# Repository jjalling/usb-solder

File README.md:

# usb-solder

USB-PD soldering iron, using Weller RT soldering tips

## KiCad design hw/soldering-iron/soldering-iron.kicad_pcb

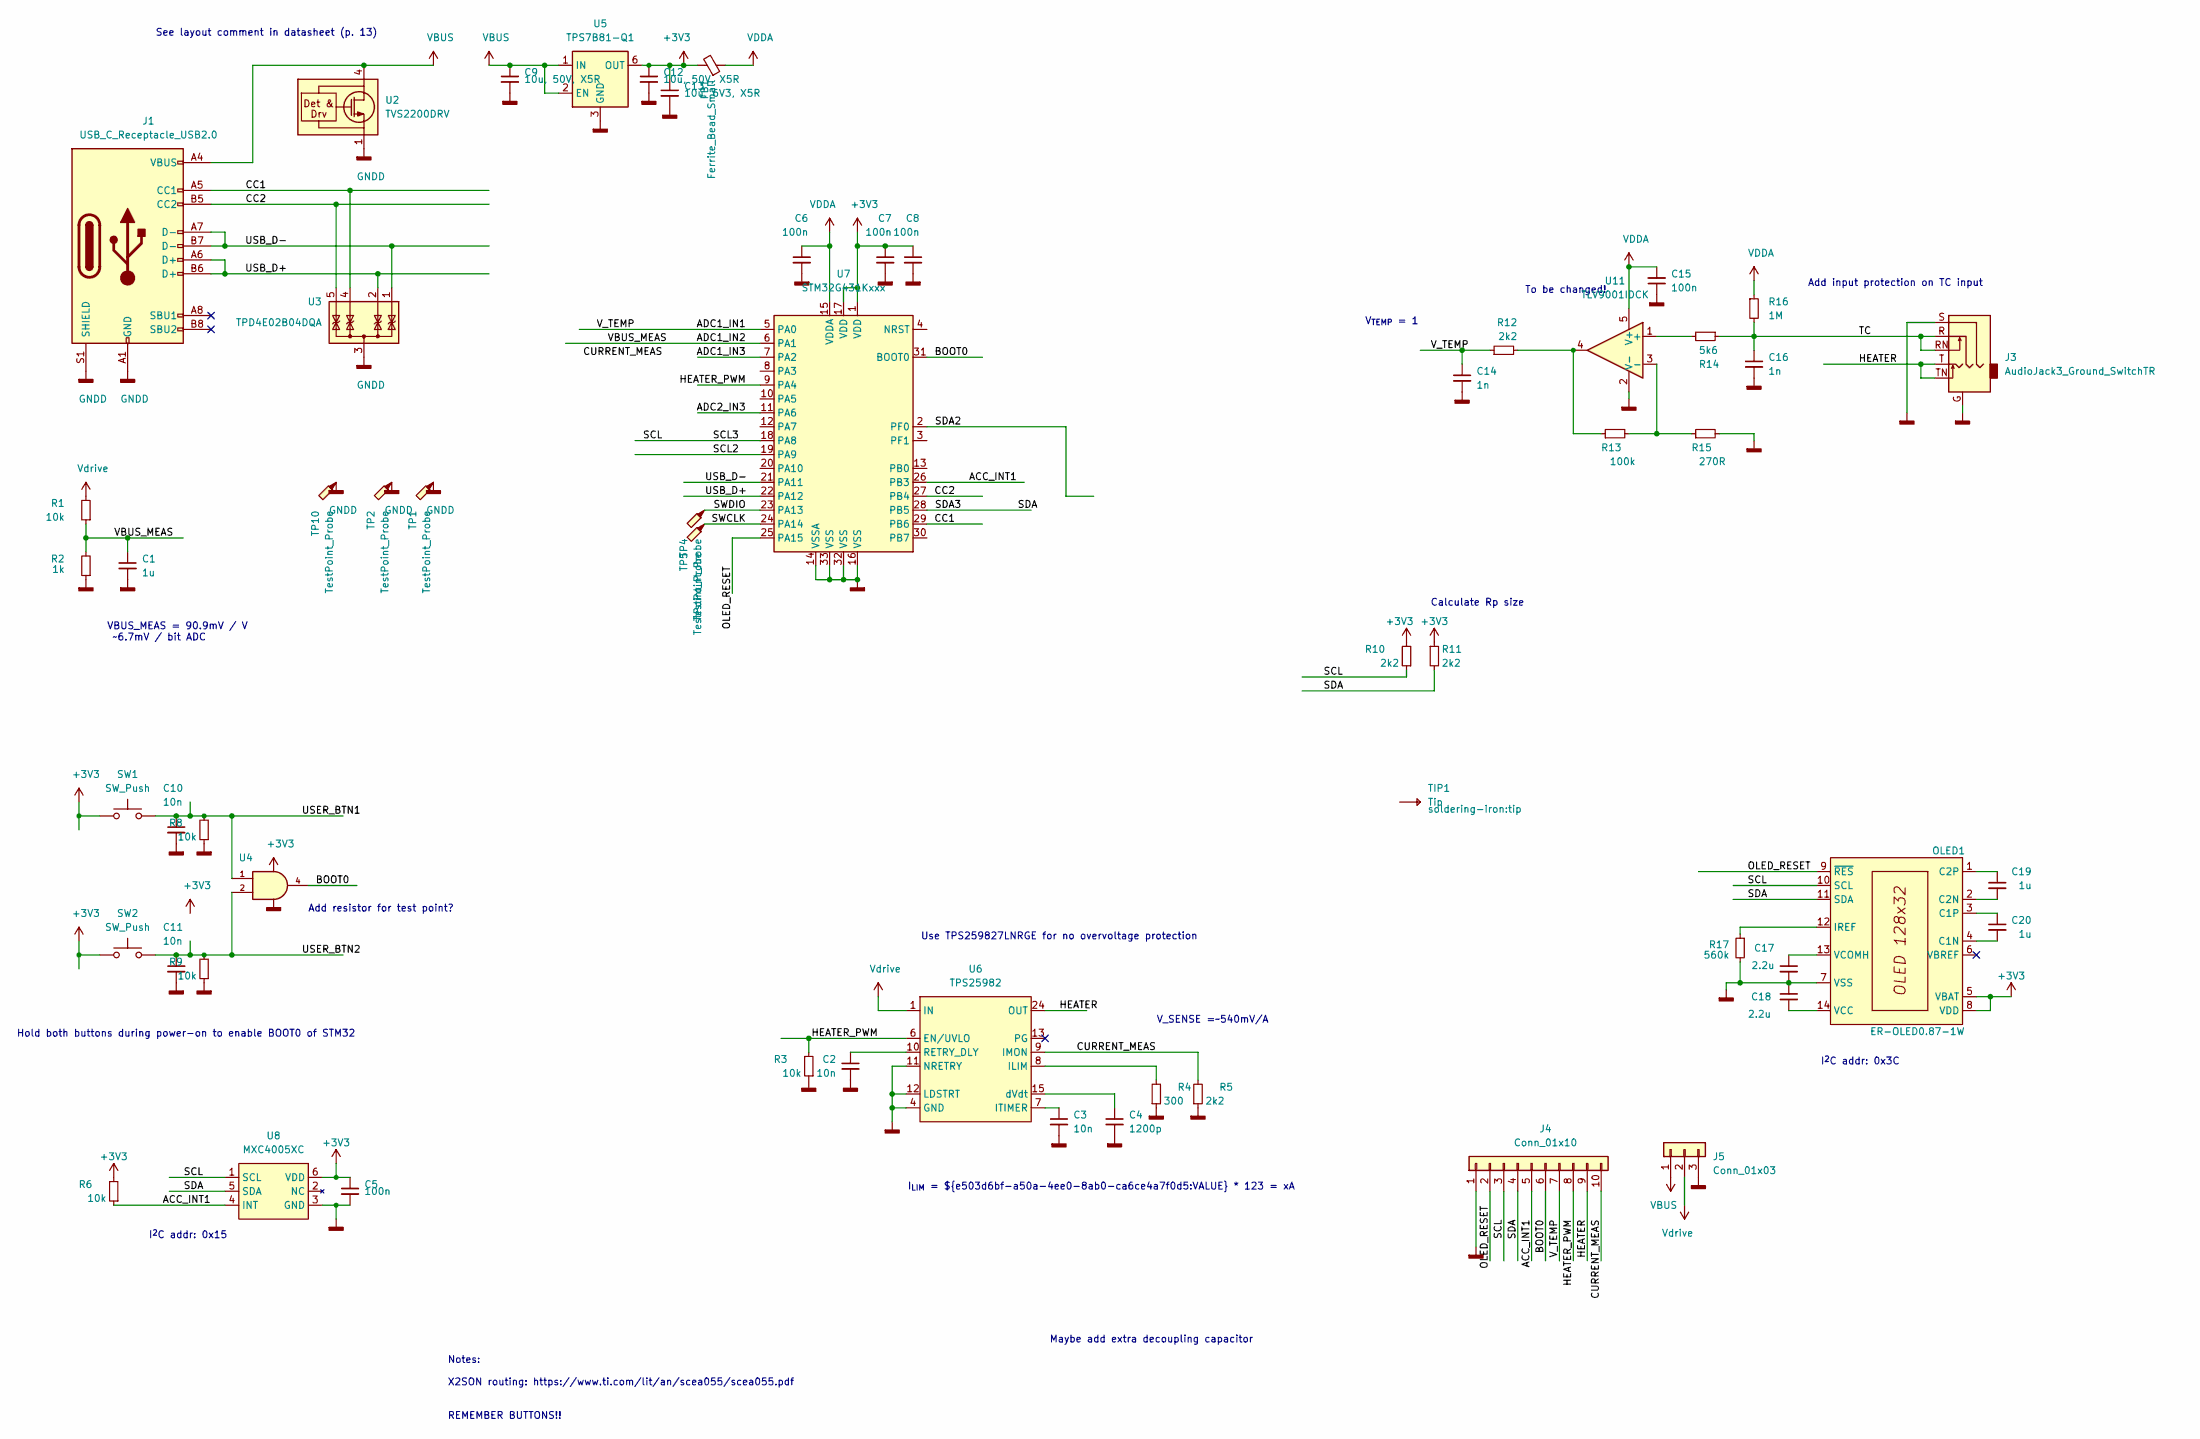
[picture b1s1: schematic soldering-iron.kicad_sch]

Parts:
C1, C19, C20: 1u; C_0402_1005Metric
C2, C3, C10, C11: 10n; C_0402_1005Metric
C4: 1200p; C_0402_1005Metric
C5, C6, C7, C8, C15: 100n; C_0402_1005Metric
C9, C12: 10u, 50V, X5R; C_0805_2012Metric
C13: 10u, 6V3, X5R; C_0402_1005Metric
C14, C16: 1n; C_0402_1005Metric
C17, C18: 2.2u; C_0402_1005Metric
FB1: Ferrite_Bead_Small; L_0402_1005Metric
J1: USB_C_Receptacle_USB2.0; DX07S016JA1R1500
J3: AudioJack3_Ground_SwitchTR; SJ-43504-SMT
J4: Conn_01x10; PinHeader_1x10_P2.54mm_Vertical
J5: Conn_01x03; PinHeader_1x03_P2.54mm_Vertical
OLED1: ER-OLED0.87-1W; ER-OLED0.87-1-straight
R1, R3, R6, R8, R9: 10k; R_0402_1005Metric
R2: 1k; R_0402_1005Metric
R4: 300; R_0402_1005Metric
R5, R10, R11, R12: 2k2; R_0402_1005Metric
R13: 100k; R_0402_1005Metric
R14: 5k6; R_0402_1005Metric
R15: 270R; R_0402_1005Metric
R16: 1M; R_0402_1005Metric
R17: 560k; R_0402_1005Metric
SW1, SW2: SW_Push; EVQP7K
TIP1: Tip; tip
TP1, TP2, TP10: TestPoint_Probe; PinHeader_1x01_P2.54mm_Vertical
TP4, TP5: TestPoint_Probe; TestPoint_Pad_D1.0mm
U2: TVS2200DRV; WSON-6-1EP_2x2mm_P0.65mm_EP1x1.6mm
U3: TPD4E02B04DQA; USON-10_2.5x1.0mm_P0.5mm
U4: 74LVC1G08; SOT-23-5
U5: TPS7B81-Q1; WSON-6-1EP_2x2mm_P0.65mm_EP1x1.6mm
U6: TPS25982; VQFN-24-1EP_4x4mm_P0.5mm_EP2.45x2.45mm_ThermalVias
U7: STM32G431Kxxx; LQFP-32_7x7mm_P0.8mm
U8: MXC4005XC; MXC400xXC
U11: TLV9001IDCK; SOT-353_SC-70-5

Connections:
+3V3: C5.1, C7.1, C8.1, C12.1, C13.1, FB1.2, OLED1.5 (VBAT), OLED1.8 (VDD), R6.2, R10.2, R11.1, SW1.1, SW2.1, U4.5 (VCC), U5.6 (OUT), U7.1 (VDD), U7.17 (VDD), U8.6 (VDD)
/ACC_INT1: J4.5, R6.1, U7.26 (PB3), U8.4 (INT)
/ADC1_IN1: C14.1, J4.7, R12.1, U7.5 (PA0)
/ADC1_IN2: C1.1, R1.1, R2.2, U7.6 (PA1)
/ADC1_IN3: U7.7 (PA2)
/ADC2_IN3: U7.11 (PA6)
/BOOT0: J4.6, U4.4, U7.31 (BOOT0)
/CC1: J1.A5 (CC1), U3.4 (IO3), U3.7 (NC), U7.29 (PB6)
/CC2: J1.B5 (CC2), U3.5 (IO4), U3.6 (NC), U7.27 (PB4)
/CURRENT_MEAS: J4.10, R5.2, U6.9 (IMON)
/HEATER: J3.T, J3.TN, J4.9, U6.17 (OUT), U6.18 (OUT), U6.19 (OUT), U6.20 (OUT), U6.21 (OUT), U6.22 (OUT), U6.23 (OUT), U6.24 (OUT)
/HEATER_PWM: J4.8, R3.2, U6.6 (EN/UVLO), U7.9 (PA4)
/OLED_RESET: J4.2, OLED1.9 (~RES), U7.25 (PA15)
/SCL: J4.3, OLED1.10 (SCL), R10.1, U7.18 (PA8), U8.1 (SCL)
/SCL2: U7.19 (PA9)
/SDA: J4.4, OLED1.11 (SDA), R11.2, U7.28 (PB5), U8.5 (SDA)
/SDA2: U7.2 (PF0)
/SWCLK: TP5.1, U7.24 (PA14)
/SWDIO: TP4.1, U7.23 (PA13)
/TC: C16.1, J3.R, J3.RN, R14.1, R16.2
/USB_D+: J1.A6 (D+), J1.B6 (D+), U3.2 (IO2), U3.9 (NC), U7.22 (PA12)
/USB_D-: J1.A7 (D-), J1.B7 (D-), U3.1 (IO1), U3.10 (NC), U7.21 (PA11)
/USER_BTN1: C10.1, R8.2, SW1.2, U4.1
/USER_BTN2: C11.1, R9.2, SW2.2, U4.2
GND: C1.2, C2.2, C3.2, C4.2, C5.2, C6.2, C7.2, C8.2, C9.2, C10.2, C11.2, C12.2, C13.2, C14.2, C15.1, C16.2, C17.2, C18.1, J1.A1 (GND), J1.A12 (GND), J1.B1 (GND), J1.B12 (GND), J1.S1 (SHIELD), J3.G, J3.S, J4.1, J5.3, OLED1.7 (VSS), R2.1, R3.1, R4.1, R5.1, R8.1, R9.1, R15.2, R17.2, TP1.1, TP2.1, TP10.1, U2.1 (GND), U2.2 (GND), U2.3 (GND), U2.7 (GND), U3.3 (G), U3.8 (G), U4.3 (GND), U5.3 (GND), U5.4 (GND), U5.7 (GND), U6.4 (GND), U6.5 (GND), U6.11 (NRETRY), U6.12 (LDSTRT), U6.14 (GND), U6.26 (GND), U7.14 (VSSA), U7.16 (VSS), U7.32 (VSS), U7.33 (VSS), U8.3 (GND), U11.2 (V-)
IN: J5.2, R1.2, U6.1 (IN), U6.2 (IN), U6.3 (IN), U6.16 (IN), U6.25 (IN)
unnamed: C2.1, U6.10 (RETRY_DLY)
unnamed: C3.1, U6.7 (ITIMER)
unnamed: C4.1, U6.15 (dVdt)
unnamed: C17.1, OLED1.13 (VCOMH)
unnamed: C18.2, OLED1.14 (VCC)
unnamed: C19.1, OLED1.1 (C2P)
unnamed: C19.2, OLED1.2 (C2N)
unnamed: C20.1, OLED1.3 (C1P)
unnamed: C20.2, OLED1.4 (C1N)
unnamed: OLED1.12 (IREF), R17.1
unnamed: R4.2, U6.8 (ILIM)
unnamed: R12.2, R13.1, U11.4
unnamed: R13.2, R15.1, U11.3 (-)
unnamed: R14.2, U11.1 (+)
VBUS: C9.1, J1.A4 (VBUS), J1.A9 (VBUS), J1.B4 (VBUS), J1.B9 (VBUS), J5.1, U2.4 (IN), U2.5 (IN), U2.6 (IN), U5.1 (IN), U5.2 (EN)
VDDA: C6.1, C15.2, FB1.1, R16.1, U7.15 (VDDA), U11.5 (V+)

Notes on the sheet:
Hold both buttons during power-on to enable BOOT0 of STM32
VBUS_MEAS = 90.9mV / V ~~6.7mV / bit ADC
I^{2}C addr: 0x15
See layout comment in datasheet (p. 13)
Notes: X2SON routing: https://www.ti.com/lit/an/scea055/scea055.pdf REMEMBER BUTTONS!!
Add resistor for test point?
V_SENSE =~~540mV/A
Use TPS259827LNRGE for no overvoltage protection
Maybe add extra decoupling capacitor
I_{LIM} = ${e503d6bf-a50a-4ee0-8ab0-ca6ce4a7f0d5:VALUE} * 123 = xA
V_{TEMP} = 1
To be changed!
Calculate Rp size
I^{2}C addr: 0x3C
Add input protection on TC input

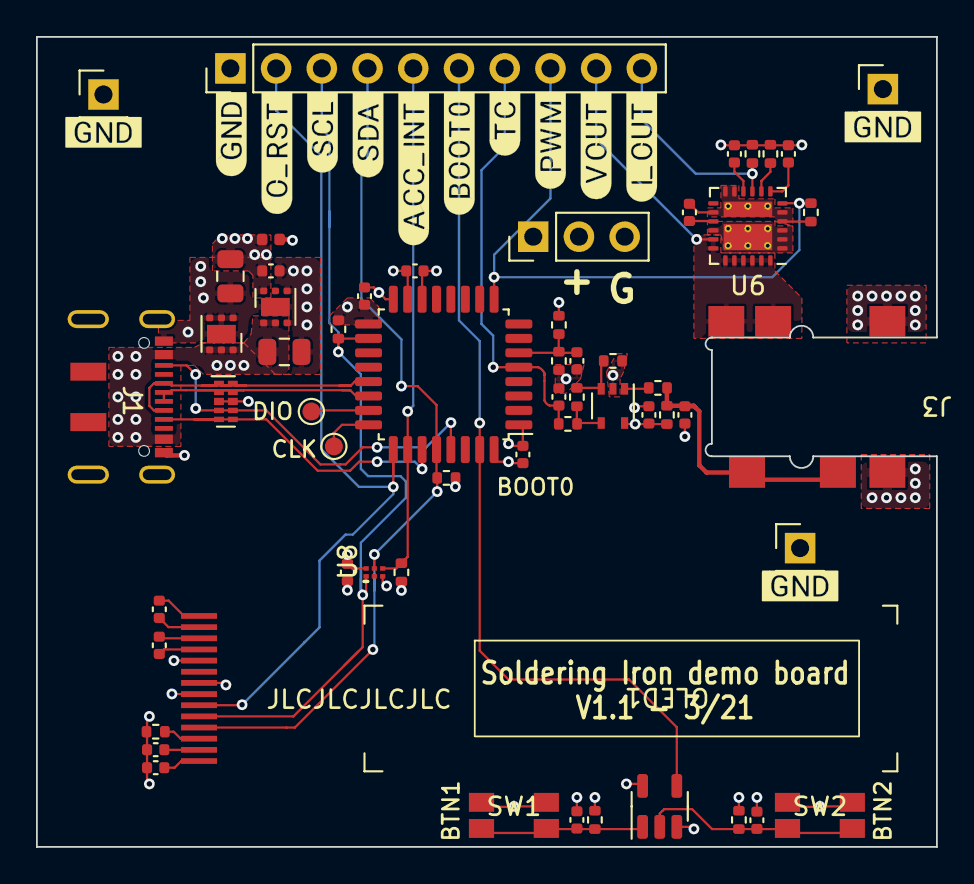
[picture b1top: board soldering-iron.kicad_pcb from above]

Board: 4 copper layers, 50.0 x 45.0 mm, 57 parts (0 on the bottom side), 38 nets.

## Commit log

2021-03-20 "more info in README"
2021-03-21 Initial schematic
2021-03-23 Modified pcb for dev-board
